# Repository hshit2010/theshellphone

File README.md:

# shell phone

## Introduction to me 

Hi i am Harshit and i am a teen who loves to code i have been coding since age 10 with the inspiration of iron man and i love to build stuff and now i am making stuff so recently i have been doing much of software stuff and i have recorded coding hours of 26 approx and i got bored of it so I am here doing hardware hope you enjoy ;)

## Introduction to project

* **what it is:** so i recently came across a anime the goated anime **One piece** and I found the den den mushi (transponder snail) very appealing so i decided to build one for me the cute little snail with my very own touch i added custom finishes like Luffys's straw hat(mugiwara) and straw hat pirate flag and stuff

* **How it works:** According to me it works using bluetooth connectivity you connect it to your phone and start typing the phone number and the moment you hit the ***`10th digit`*** it calls the number.

* **what's the purpose:** The purpose is to enjoy the anime while having a piece of anime for our own

* **Why it exists:** I watched a reel of a creator making a transponder snail for themself which gave me the idea to make one for myself also.

* **Why I made it:** I personally made it to tackle my fear of 3D models and stuff in autodesk360 but after this project I can say i really improved my skills.

## B.O.M

## Pictures

## How to assemble

 The snail body itself is divided into two bodies so follow these steps:
 
1) Take the PCB and place it on the back side of the hole on the right side of the body and screw the screw from inside out in such a way that the PCB is mounted and hold using screw head use the smaller nail set for this.
2) Solder the 7 pin connector and stuff to the PCB
3) Place the esp 32 at bottom and connect the esp32 pins to the 7 pin connector of the PCB using wires or jumper cables.
4) now place the screen from inside out and connect it to the esp 32
5) same for speaker , amplifier, mic.
6) now from the back hole slide the USB-C cable and connect the ESP-32
7) Now using the longer screw set and screw the two bodies together

**pro tip:** while screwing the screws in use the brass-heat set insert which can be pushed inside the screw holes by placing it on top and using the solder heat and push the insert in the hole so it is easier to hold them.

## How to flash

You can use the arduino IDE and other softwares for this task

## Known issues:
1) there are two big holes from the front i left them for the heat to pass and also to show and flex the wires and stuff as i find it cool(don't judge me ;) )
2) the firmware is little poor as I didn't even knew c++ before it so the code could be bad.
3) the holes for some substances might be size miss match due to my inexperience in Autodesk360

## Credits

MIT you can use it as much as you like  copy it ,download it ,use it but while sharing don't forget to tag me or give me credit and make sure to star this repo.

## My contacts

Insta: **`kataria_harshit10`**

email: **`harshitkataria2010@gmail.com`**(i don't usually check my email so just DM me )

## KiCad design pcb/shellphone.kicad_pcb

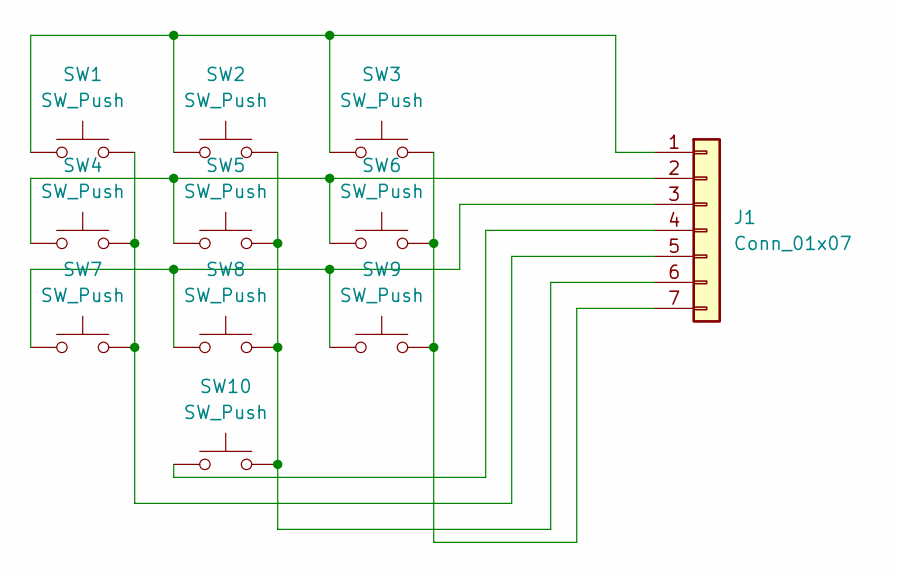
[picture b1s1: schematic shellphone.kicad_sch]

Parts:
J1: Conn_01x07; PinHeader_1x07_P2.54mm_Vertical
SW1, SW2, SW3, SW4, SW5, SW6, SW7, SW8, SW9, SW10: SW_Push; SW_Cherry_MX_1.00u_PCB

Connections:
unnamed: J1.1, SW1.1, SW2.1, SW3.1
unnamed: J1.2, SW4.1, SW5.1, SW6.1
unnamed: J1.3, SW7.1, SW8.1, SW9.1
unnamed: J1.4, SW10.1
unnamed: J1.5, SW1.2, SW4.2, SW7.2
unnamed: J1.6, SW2.2, SW5.2, SW8.2, SW10.2
unnamed: J1.7, SW3.2, SW6.2, SW9.2

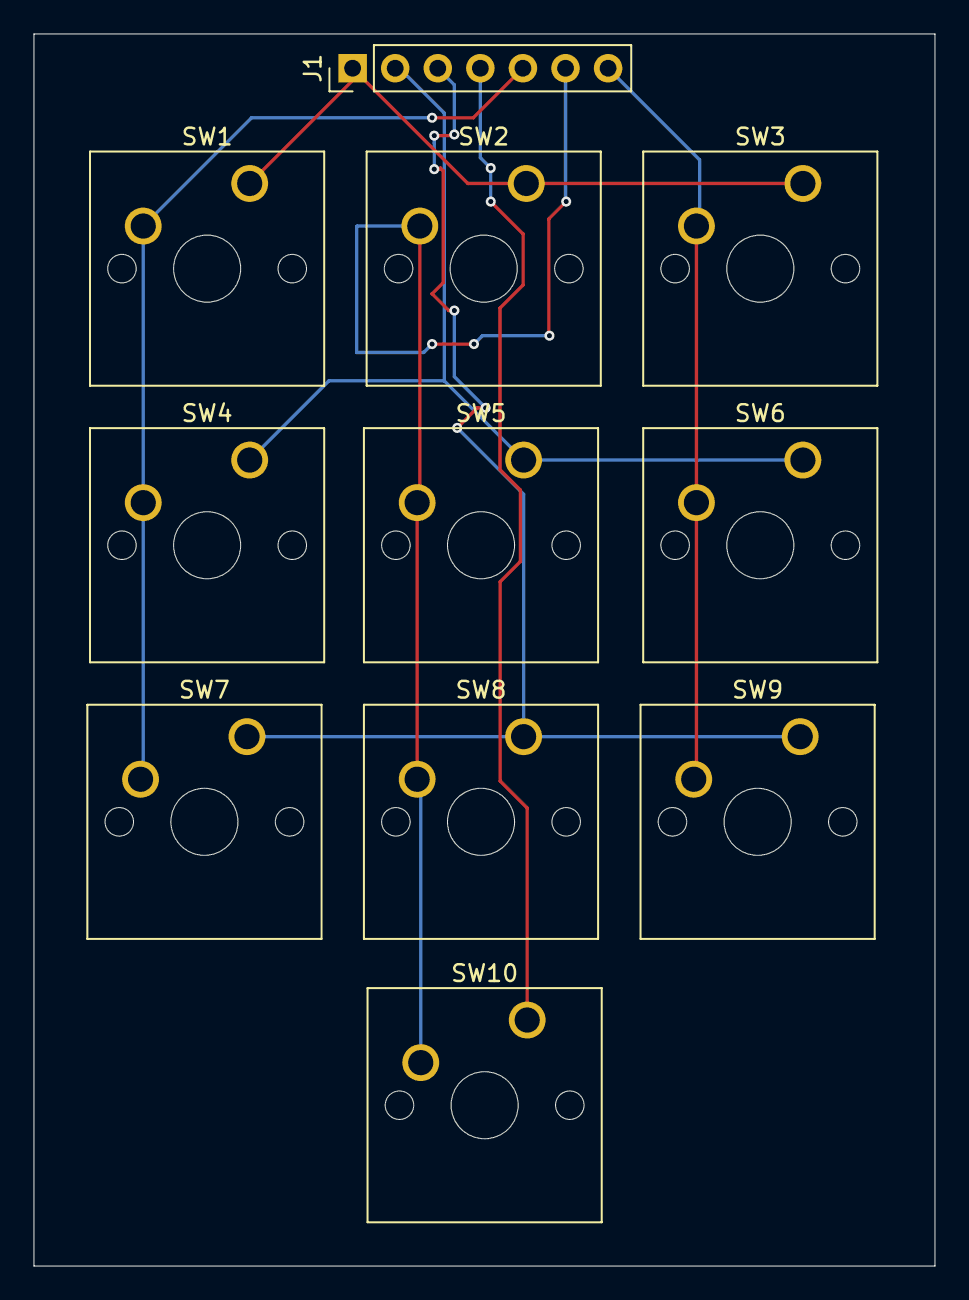
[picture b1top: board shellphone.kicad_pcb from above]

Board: 2 copper layers, 53.8 x 73.5 mm, 11 parts (0 on the bottom side), 7 nets.
